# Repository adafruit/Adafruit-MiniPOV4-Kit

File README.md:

MiniPOV4-Kit with Linux support
===============================

Files, Firmware and Software for the MiniPOV4 color light-painting kit
Pick up a kit here: https://www.adafruit.com/products/1776

The latest and greatest MiniPOV kit to hit the streets - MiniPOV4! We have added full color RGB LEDs to the kit as well USB programmability to make this the easiest, most fun Persistence-of-Vision & Light Painting kit ever.

Learn to solder by building this easy kit. About 30 components are soldered onto the custom PCB using a soldering iron, solder and some basic hand tools such as diagonal cutters and wire strippers. Learn as you go, starting with the easier parts and working your way up to the more challenging ones. Takes about an hour or two to complete following our detailed tutorial, depending on your previous soldering experience. 

* Firmware: The Arduino-IDE compatible firmware that draws images from EEPROM

* Hardware: PCB files in Eagle CAD format

* Images: some test pix we use

* Bootloader: The V-USB based bootloader that lets you program the EEPROM over USB for uploading new images.

* MiniPov4_ImageConverter: The image uploader, for use with Processing 2.x! 

Now with linux support: install your distribution's version of avrdude and the MiniPov4_ImageConverter should work.

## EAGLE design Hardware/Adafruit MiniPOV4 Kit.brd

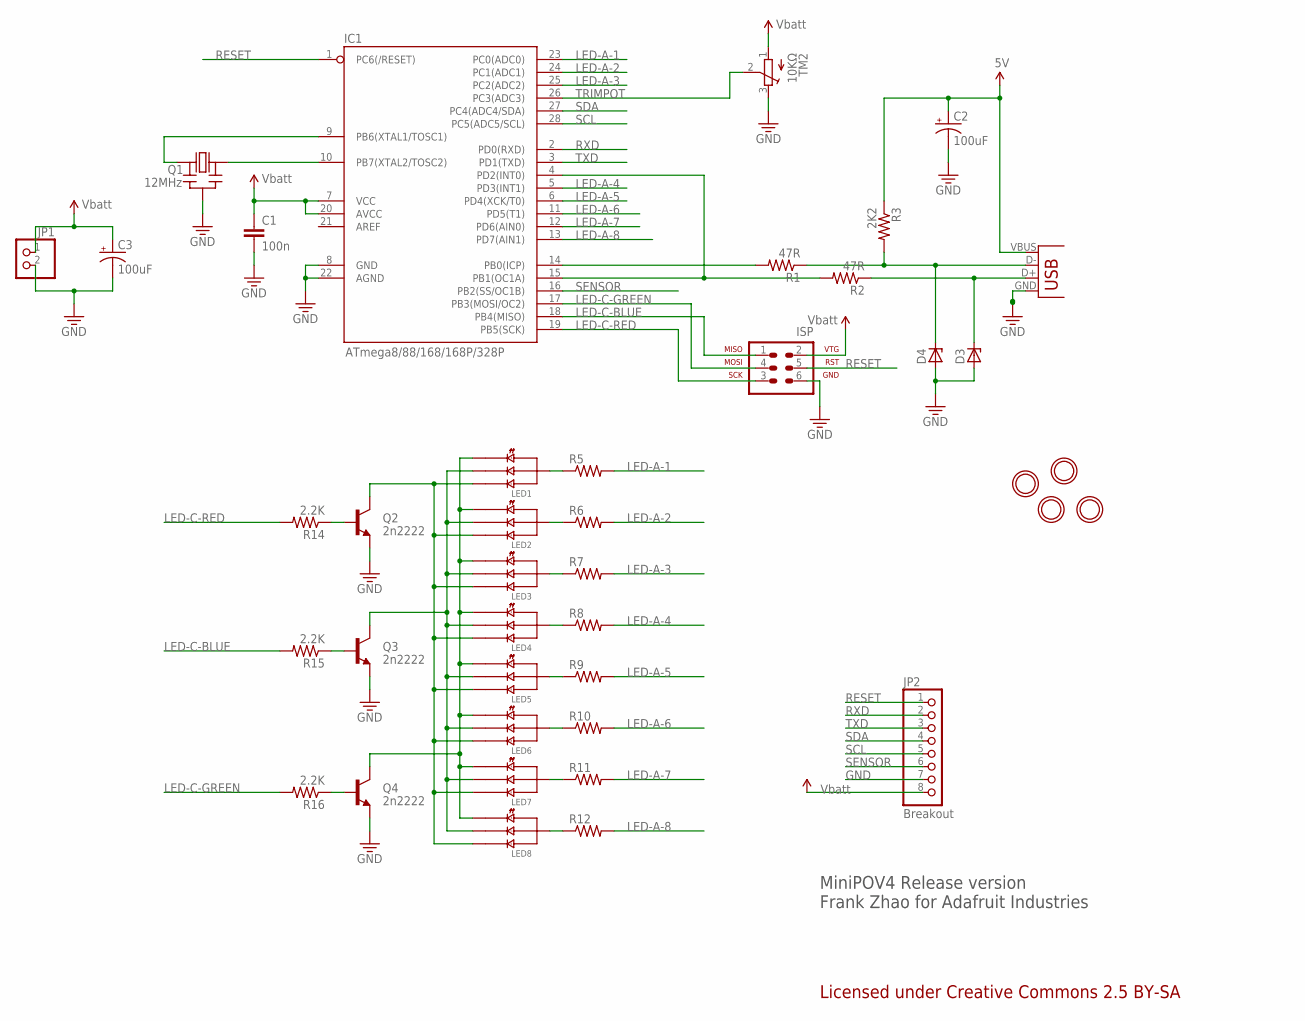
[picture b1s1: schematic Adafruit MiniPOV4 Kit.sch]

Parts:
C1: 100n; CAP-PTH-SMALL2
C2, C3: 100uF; E2,5-6
D3, D4: ZENER-DIODEDO34-7; DO34Z7
IC1: ATmega8/88/168/168P/328P; DIL28-3
ISP: AVR-ISP-6
JP1: HEADER-1X2; 1X02_OVAL
JP2: Breakout; 1X08-BIG
LED1, LED2, LED3, LED4, LED5, LED6, LED7, LED8: LED-RGB-CA-PIRANHA; PIRANHA5MM
Q1: 12MHz; CERM_OSC
Q2, Q3, Q4: 2n2222; TO-92
R1, R2: 47R; 0207/9
R3: 2K2; 0207/9
R5, R6, R7, R8, R9, R10, R11, R12: R-US_0207/9; 0207/9
R14, R15, R16: 2.2K; 0207/9
TM2: 10KΩ; TRIM-3386
U$2, U$3, U$4, U$5: MOUNTINGHOLE2.5_THICK; MOUNTINGHOLE_2.5_PLATED_THICK
USB: USBPTH; USB-B-PTH

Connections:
3.3V: C1.1, C3.+, IC1.7 (VCC), IC1.20 (AVCC), ISP.2 (VTG), JP1.1, JP2.8, TM2.1 (A)
5V: C2.+, R3.1, USB.VBUS
GND: C1.2, C2.-, C3.-, D3.A, D4.A, IC1.8 (GND), IC1.22 (AGND), ISP.6 (GND), JP1.2, JP2.7, Q1.G (GND), Q2.1 (E), Q3.1 (E), Q4.1 (E), TM2.3 (E), USB.GND, USB.S1, USB.S2
LED-A-1: IC1.23 (PC0(ADC0)), R5.2
LED-A-2: IC1.24 (PC1(ADC1)), R6.2
LED-A-3: IC1.25 (PC2(ADC2)), R7.2
LED-A-4: IC1.5 (PD3(INT1)), R8.2
LED-A-5: IC1.6 (PD4(XCK/T0)), R9.2
LED-A-6: IC1.11 (PD5(T1)), R10.2
LED-A-7: IC1.12 (PD6(AIN0)), R11.2
LED-A-8: IC1.13 (PD7(AIN1)), R12.2
LED-C-BLUE: IC1.18 (PB4(MISO)), ISP.1 (MISO), R15.2
LED-C-GREEN: IC1.17 (PB3(MOSI/OC2)), ISP.4 (MOSI), R16.2
LED-C-RED: IC1.19 (PB5(SCK)), ISP.3 (SCK), R14.2
unnamed: IC1.9 (PB6(XTAL1/TOSC1)), Q1.1 (IN)
unnamed: IC1.10 (PB7(XTAL2/TOSC2)), Q1.2 (OUT)
unnamed: D4.C, R1.1, R3.2, USB.D-
unnamed: D3.C, R2.1, USB.D+
unnamed: LED2.4 (C), R6.1
unnamed: LED1.4 (C), R5.1
unnamed: IC1.14 (PB0(ICP)), R1.2
unnamed: IC1.4 (PD2(INT0)), IC1.15 (PB1(OC1A)), R2.2
unnamed: LED8.4 (C), R12.1
unnamed: LED7.4 (C), R11.1
unnamed: LED6.4 (C), R10.1
unnamed: LED5.4 (C), R9.1
unnamed: LED4.4 (C), R8.1
unnamed: LED3.4 (C), R7.1
unnamed: LED1.2 (R), LED2.2 (R), LED3.2 (R), LED4.2 (R), LED5.2 (R), LED6.2 (R), LED7.2 (R), LED8.2 (R), Q4.3 (C)
unnamed: LED1.3 (G), LED2.3 (G), LED3.3 (G), LED4.3 (G), LED5.3 (G), LED6.3 (G), LED7.3 (G), LED8.3 (G), Q3.3 (C)
unnamed: LED1.1 (B), LED2.1 (B), LED3.1 (B), LED4.1 (B), LED5.1 (B), LED6.1 (B), LED7.1 (B), LED8.1 (B), Q2.3 (C)
unnamed: Q2.2 (B), R14.1
unnamed: Q3.2 (B), R15.1
unnamed: Q4.2 (B), R16.1
RESET: IC1.1 (PC6(/RESET)), ISP.5 (RST), JP2.1
RXD: IC1.2 (PD0(RXD)), JP2.2
SCL: IC1.28 (PC5(ADC5/SCL)), JP2.5
SDA: IC1.27 (PC4(ADC4/SDA)), JP2.4
SENSOR: IC1.16 (PB2(SS/OC1B)), JP2.6
TRIMPOT: IC1.26 (PC3(ADC3)), TM2.2 (S)
TXD: IC1.3 (PD1(TXD)), JP2.3

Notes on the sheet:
MiniPOV4 Release version Frank Zhao for Adafruit Industries
Licensed under Creative Commons 2.5 BY-SA

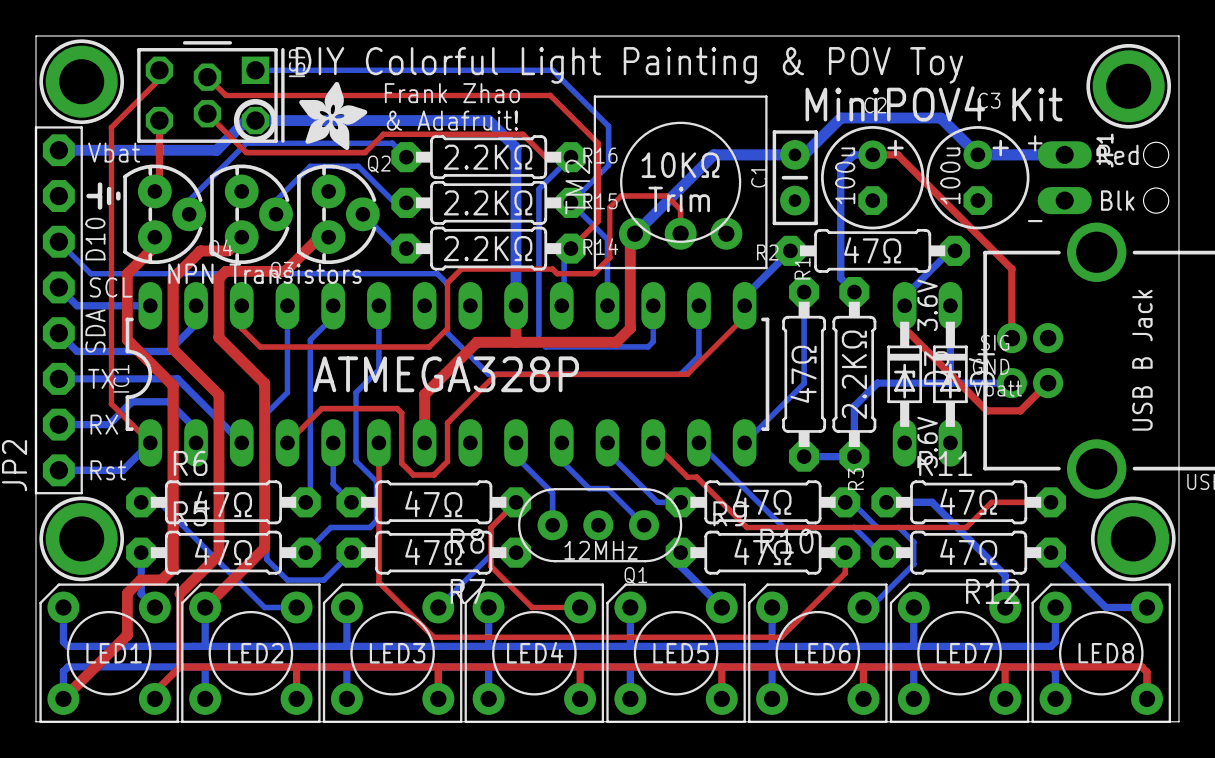
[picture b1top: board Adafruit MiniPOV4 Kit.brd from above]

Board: 2 copper layers, 63.5 x 38.1 mm, 42 parts (0 on the bottom side), 41 nets.

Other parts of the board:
U$6: ADAFRUIT_3.5MM

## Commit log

2014-04-25 Core firmware
2014-04-25 Final hardware
2014-04-25 bootloader & test images
2014-04-25 added software and readm
2014-04-25 i dont know markdown can you tell???
2014-04-26 oh yeah, mac support!
2016-12-30 Processing dir and Sketch name must be equal
2016-12-30 Linux support
2016-12-30 be more verbose on linux when something fails.
2016-12-30 Adjust readme to reflect difference to mainline

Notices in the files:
parts and their libraries:
microbuilder: This work is placed in the public domain, and may be freely used for commercial and non-commercial work with the following conditions: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
